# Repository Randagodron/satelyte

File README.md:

# satelyte
Experimental distortion for electric guitar

Based on the Fulltone OCD and the Crowther Audio Prunes & Custard, with an additional octaver.

CAD done with KiCAD, simulation done with LTSpice.

Companion article (in french) : http://blog.randagodron.eu/index.php?post/2017/05/25/DIY-audio-Satelyte

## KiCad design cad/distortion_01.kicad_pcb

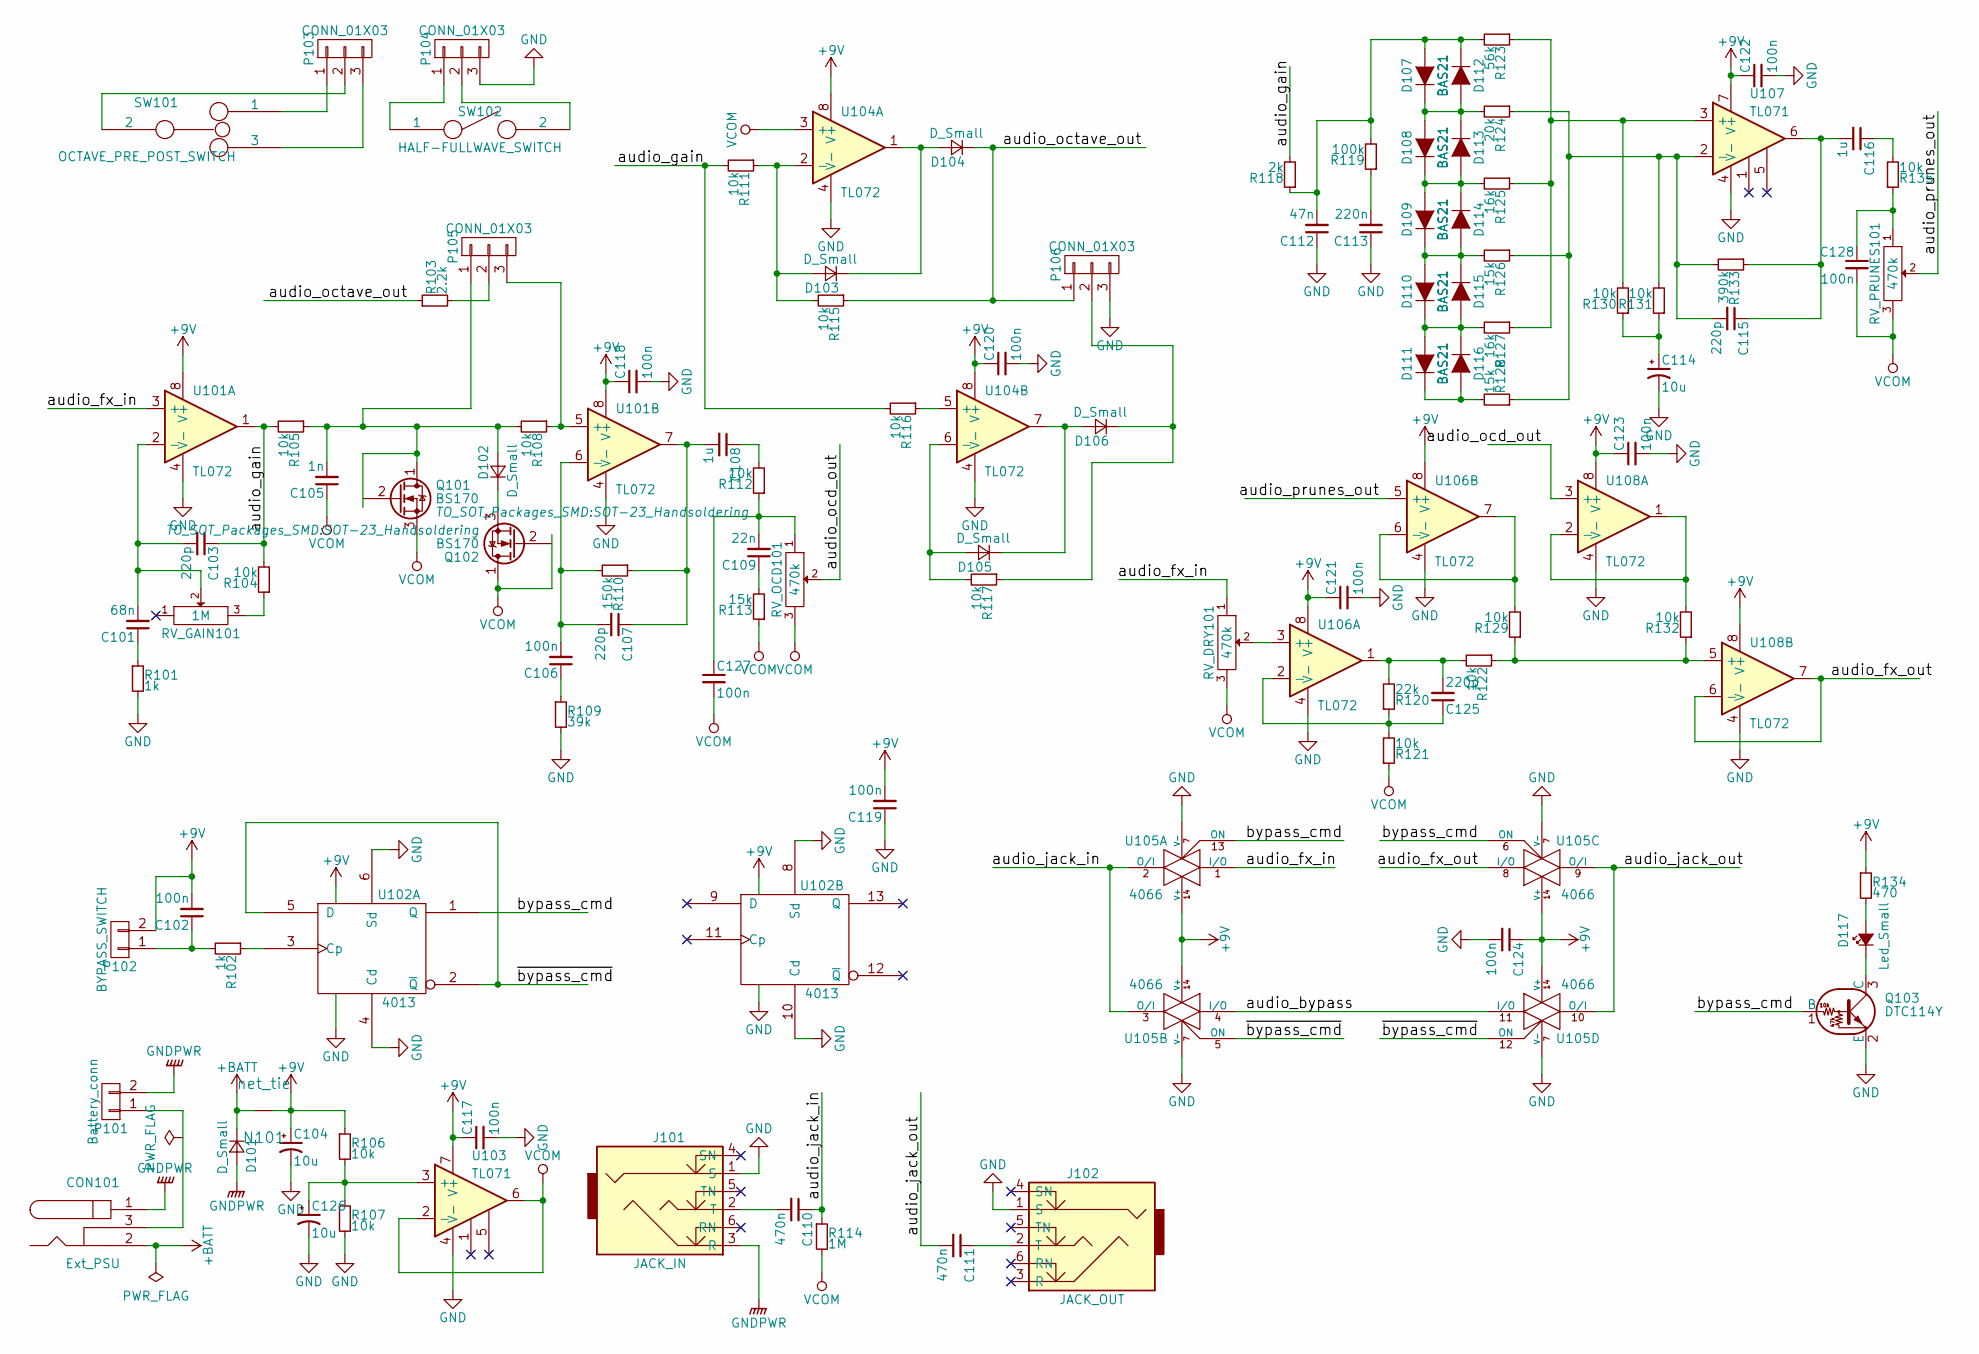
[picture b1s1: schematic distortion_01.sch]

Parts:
C101: 68n; C_0603_HandSoldering
C102, C106, C117, C118, C119, C120, C121, C122, C123, C124, C127, C128: 100n; C_0603_HandSoldering
C103, C107, C115, C125: 220p; C_0603_HandSoldering
C104, C114, C126: 10u; CP_Elec_5x4.5
C105: 1n; C_0603_HandSoldering
C108, C116: 1u; C_0805_HandSoldering
C109: 22n; C_0603_HandSoldering
C110, C111: 470n; C_0805_HandSoldering
C112: 47n; C_0603_HandSoldering
C113: 220n; C_0603_HandSoldering
CON101: Ext_PSU; Pin_Header_Straight_1x03_Pitch2.54mm
D101: D_Small; D_SMA_Handsoldering
D102, D103, D104, D105, D106: D_Small; SOT-23_Handsoldering
D107, D108, D109, D110, D111, D112, D113, D114, D115, D116: BAS21; SOT-23
D117: Led_Small; Pin_Header_Straight_1x02_Pitch2.54mm
J101: JACK_IN; NMJ6HCD2
J102: JACK_OUT; NMJ6HCD2
N101: net_tie; net_tie_0.5mm
P101: Battery_conn; Pin_Header_Straight_1x02_Pitch2.54mm
P102: BYPASS_SWITCH; Pin_Header_Straight_1x02_Pitch2.54mm
P103, P104, P105, P106: CONN_01X03; Pin_Header_Straight_1x03_Pitch2.54mm
Q101, Q102: BS170; SOT-23_Handsoldering
Q103: DTC114Y; SOT-23_Handsoldering
R101, R102: 1k; R_0603_HandSoldering
R103: 2.2k; R_0603_HandSoldering
R104, R105, R106, R107, R108, R111, R112, R115, R116, R117, R121, R122, R129, R130, R131, R132, R135: 10k; R_0603_HandSoldering
R109: 39k; R_0603_HandSoldering
R110: 150k; R_0603_HandSoldering
R113, R126, R128: 15k; R_0603_HandSoldering
R114: 1M; R_0603_HandSoldering
R118: 2k; R_0603_HandSoldering
R119: 100k; R_0603_HandSoldering
R120: 22k; R_0603_HandSoldering
R123: 56k; R_0603_HandSoldering
R124: 20k; R_0603_HandSoldering
R125, R127: 16k; R_0603_HandSoldering
R133: 390k; R_0603_HandSoldering
R134: 470; R_0805_HandSoldering
RV_DRY101: 470k; PTV09
RV_GAIN101: 1M; PTV09
RV_OCD101: 470k; PTV09
RV_PRUNES101: 470k; PTV09
SW101: OCTAVE_PRE_POST_SWITCH; SW_SPDT_through_hole
SW102: HALF-FULLWAVE_SWITCH; SW_SPDT_through_hole
U101, U104, U106, U108: TL072; SOIC-8-N
U102: 4013; SOIC-14_N
U103, U107: TL071; SOIC-8-N
U105: 4066; SOIC-14_N

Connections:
+9V: C102.2, C104.1, C117.1, C118.1, C119.2, C120.1, C121.1, C122.1, C123.1, C124.1, N101.2, P102.2, R106.1, R134.1, U101.8 (V+), U102.14 (VDD), U103.7 (V+), U104.8 (V+), U105.14 (V+), U106.8 (V+), U107.7 (V+), U108.8 (V+)
+BATT: CON101.2, D101.1 (K), N101.1
/audio_bypass: U105.4 (I/O), U105.11 (I/O)
/audio_fx_in: RV_DRY101.1, U101.3 (+), U105.1 (I/O)
/audio_fx_out: U105.8 (I/O), U108.6 (-), U108.7
/audio_gain: C103.1, R104.2, R105.2, R111.2, R116.2, R118.2, U101.1
/audio_jack_in: C110.1, R114.1, U105.2 (O/I), U105.3 (O/I)
/audio_jack_out: C111.2, U105.9 (O/I), U105.10 (O/I)
/audio_ocd_out: RV_OCD101.2, U108.3 (+)
/audio_octave_out: D104.1 (K), P106.1, R103.1, R115.1
/audio_prunes_out: RV_PRUNES101.2, U106.5 (+)
/bypass_cmd: Q103.1 (B), U102.1 (Q), U105.6 (ON), U105.13 (ON)
/~bypass_cmd~: U102.2 (~Q), U102.5 (D), U105.5 (ON), U105.12 (ON)
GND: C104.2, C112.1, C113.1, C114.2, C117.2, C118.2, C119.1, C120.2, C121.2, C122.2, C123.2, C124.2, C126.2, J101.1 (S), J102.1 (S), P104.3, P106.3, Q103.2 (E), R101.2, R107.2, R109.2, U101.4 (V-), U102.4 (Cd), U102.6 (Sd), U102.7 (VSS), U102.8 (Sd), U102.10 (Cd), U103.4 (V-), U104.4 (V-), U105.7 (V-), U106.4 (V-), U107.4 (V-), U108.4 (V-)
GNDPWR: CON101.1, D101.2 (A), J101.3 (R), P101.2
unnamed: C101.1, R101.1
unnamed: C101.2, C103.2, RV_GAIN101.2, U101.2 (-)
unnamed: C102.1, P102.1, R102.2
unnamed: C105.2, D102.2 (A), P105.1, Q101.1 (D), R105.1, R108.2
unnamed: C106.1, R109.1
unnamed: C106.2, C107.2, R110.2, U101.6 (-)
unnamed: C107.1, C108.2, R110.1, U101.7
unnamed: C108.1, R112.2
unnamed: C109.1, R113.2
unnamed: C109.2, C127.1, R112.1, RV_OCD101.1
unnamed: C110.2, J101.2 (T)
unnamed: C111.1, J102.2 (T)
unnamed: C112.2, D107.1 (A), D112.3 (K), R118.1, R119.2, R123.2
unnamed: C113.2, R119.1
unnamed: C114.1, R130.1, R131.1
unnamed: C115.1, C116.2, R133.1, U107.6
unnamed: C115.2, R124.1, R126.1, R128.1, R131.2, R133.2, U107.2 (-)
unnamed: C116.1, R135.2
unnamed: C125.1, R120.1, R121.2, U106.2 (-)
unnamed: C125.2, R120.2, R122.2, U106.1
unnamed: C126.1, R106.2, R107.1, U103.3 (+)
unnamed: C128.1, R135.1, RV_PRUNES101.1
unnamed: CON101.3, P101.1
unnamed: D102.1 (K), Q102.3 (S)
unnamed: D103.1 (K), D104.2 (A), U104.1
unnamed: D103.2 (A), R111.1, R115.2, U104.2 (-)
unnamed: D105.1 (K), D106.2 (A), U104.7
unnamed: D105.2 (A), R117.2, U104.6 (-)
unnamed: D106.1 (K), P106.2, R117.1
unnamed: D107.3 (K), D108.1 (A), D112.1 (A), D113.3 (K), R124.2
unnamed: D108.3 (K), D109.1 (A), D113.1 (A), D114.3 (K), R125.2
unnamed: D109.3 (K), D110.1 (A), D114.1 (A), D115.3 (K), R126.2
unnamed: D110.3 (K), D111.1 (A), D115.1 (A), D116.3 (K), R127.2
unnamed: D111.3 (K), D116.1 (A), R128.2
unnamed: D117.1 (K), Q103.3 (C)
unnamed: D117.2 (A), R134.2
unnamed: P103.1, SW101.1
unnamed: P103.2, SW101.2
unnamed: P103.3, SW101.3
unnamed: P104.1, SW102.1
unnamed: P104.2, SW102.2
unnamed: P105.2, R103.2
unnamed: P105.3, R108.1, U101.5 (+)
unnamed: R102.1, U102.3 (Cp)
unnamed: R104.1, RV_GAIN101.3
unnamed: R116.1, U104.5 (+)
unnamed: R122.1, R129.1, R132.1, U108.5 (+)
unnamed: R123.1, R125.1, R127.1, R130.2, U107.3 (+)
unnamed: R129.2, U106.6 (-), U106.7
unnamed: R132.2, U108.1, U108.2 (-)
unnamed: RV_DRY101.2, U106.3 (+)
VCOM: C105.1, C127.2, C128.2, Q101.3 (S), Q102.1 (D), R113.1, R114.2, R121.1, RV_DRY101.3, RV_OCD101.3, RV_PRUNES101.3, U103.2 (-), U103.6, U104.3 (+)

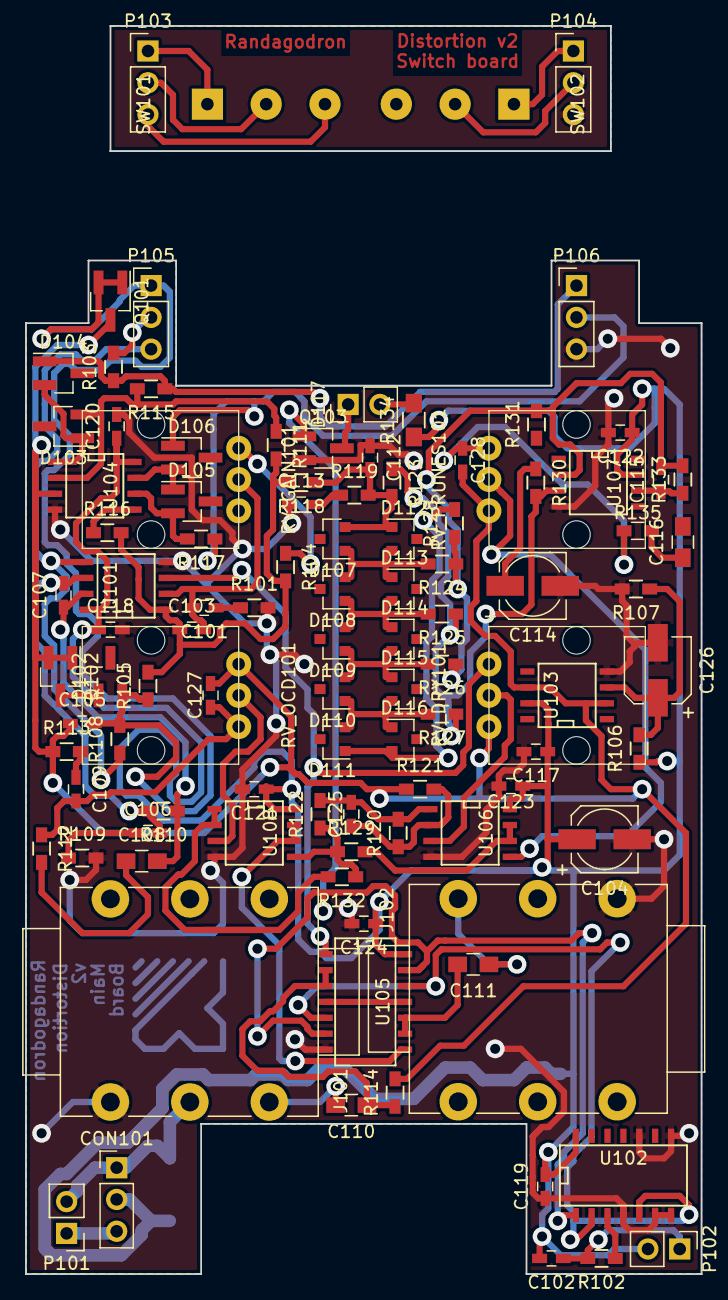
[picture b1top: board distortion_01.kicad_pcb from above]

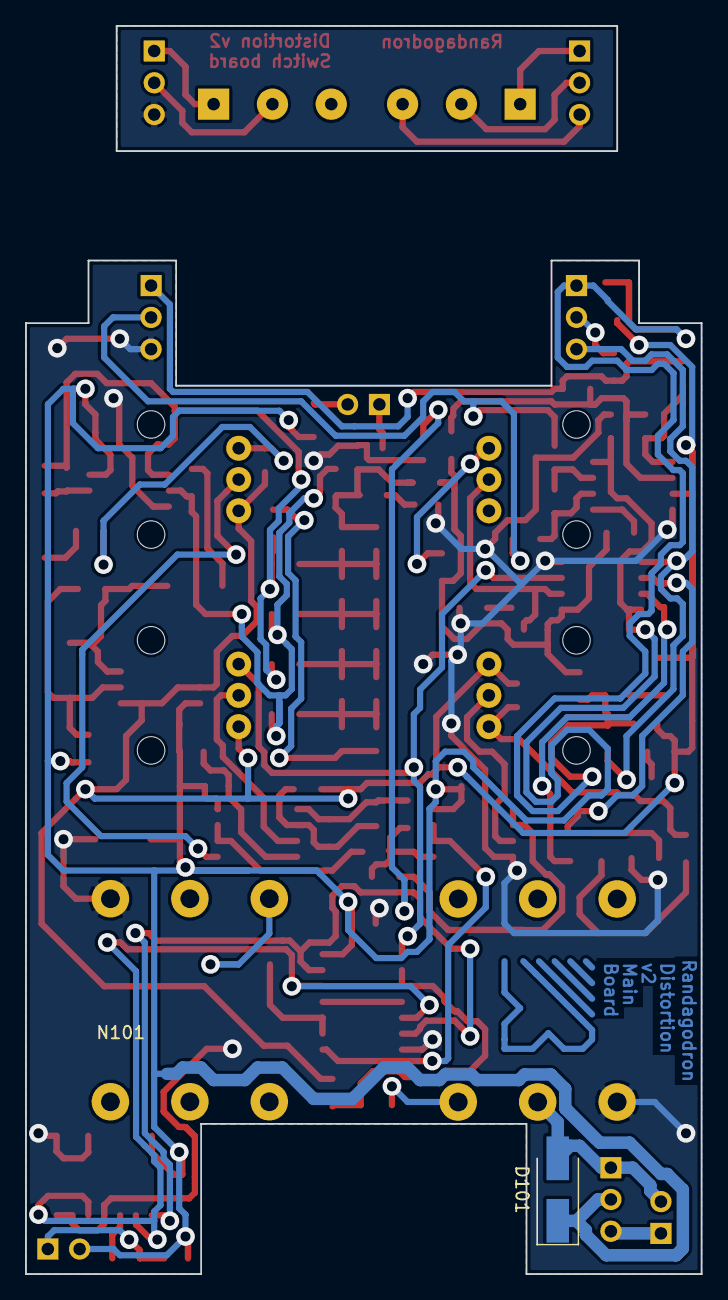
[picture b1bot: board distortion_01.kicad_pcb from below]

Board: 2 copper layers, 54.0 x 99.8 mm, 107 parts (2 on the bottom side), 67 nets.

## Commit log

2017-02-11 Added documentation.
2017-02-11 Schematic done, to be simulated.
2017-02-11 Added octave.
2017-02-12 Simulated OCD / octave part.
2017-02-12 Simulated prunes and custard with bas21 and bat54.
2017-02-12 Added gain for dry signal. Assigned footprints (TBC).
2017-02-12 Added names on pots.
2017-02-13 Placement started with 1590B cutout. Too small, 1590BB required.
2017-02-15 Changed edge cuts to 1590BB. Made pre-placement.
2017-02-25 Finished layout.
    Added switch board.
2017-02-25 Minor corrections.
2017-02-25 Started placement. Output OPA TL074 changed to 2x TL072.
2017-03-04 Added 220p capa in feedback loop of dry OPA. Placed all components on PCB.
2017-03-04 Continued layout. Changed 4066 pinout.
2017-03-22 Finished layout.
2017-03-22 Corrected layout.
2017-03-25 Corrected pots pinout and layout.
2017-03-25 Continued layout
2017-03-29 Finished layout
2017-04-01 Corrected layout. Added board name.
2017-05-11 Corrected connectors placement, switch IC and PSU connectors should be swapped for easier routing.
2017-05-13 Changed PSU connector footprint to 3w HE10, finished layout.
2017-05-13 Minor corrections on layout. Added logo.
2017-05-25 Exported layout and drill plan.
2017-09-04 Added LTspice simulation.
    Added 10n cap on OCD output.
    Added 10u cap on Vref for HF stability.
2017-09-04 Updated PCB number to v2.
2017-09-05 Corrected pots polarity (schematic and layout).
2017-09-13 Added schematics screenshots.
    Changed diodes symbols to BAS21.
2017-09-25 Added output capacitor on Prunes.
    Changed capacitor value on octave output.
    Corrected layout accordingly.
2017-09-25 Exported schematic, added topology drawing.
